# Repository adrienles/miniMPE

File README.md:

# miniMPE

An ultra-compact expressive octave-sectioned MIDI keyboard
## Idea

Originally inspired by the KORG nanoKeys line of ultra-compact MIDI keyboards, I wanted to design an alternative, with a few improvements:

- Standard key width
- Velocity sensitivity
    - The nanoKeys is not velocity sensitive, as it uses rubber-dome-like keys.
- RGB lighting for scale highlighting and pretty effects
- Daisy-chainable design, to go beyond a 2 octave design
    - This will likely be done using magnetic pogo pin connectors, for an easy and durable connection.
- Open Source :)
## Sub-projects
### MCU Test Board
This is a 4-layer test PCB designed to test one of the chosen MCU picks, alongside its dual USB peripherals, which this project might utilize.

#### Specs
- STM32F407 MCU
    - Dual USB peripherals
- IO header with dual SPI and 16 analog channels
- Dual USB ports
    - Output is protected against over-voltage
- Impedance matched USB and digital signals
- 4-layer design (Signal - Power/Gnd - Gnd - Signal)

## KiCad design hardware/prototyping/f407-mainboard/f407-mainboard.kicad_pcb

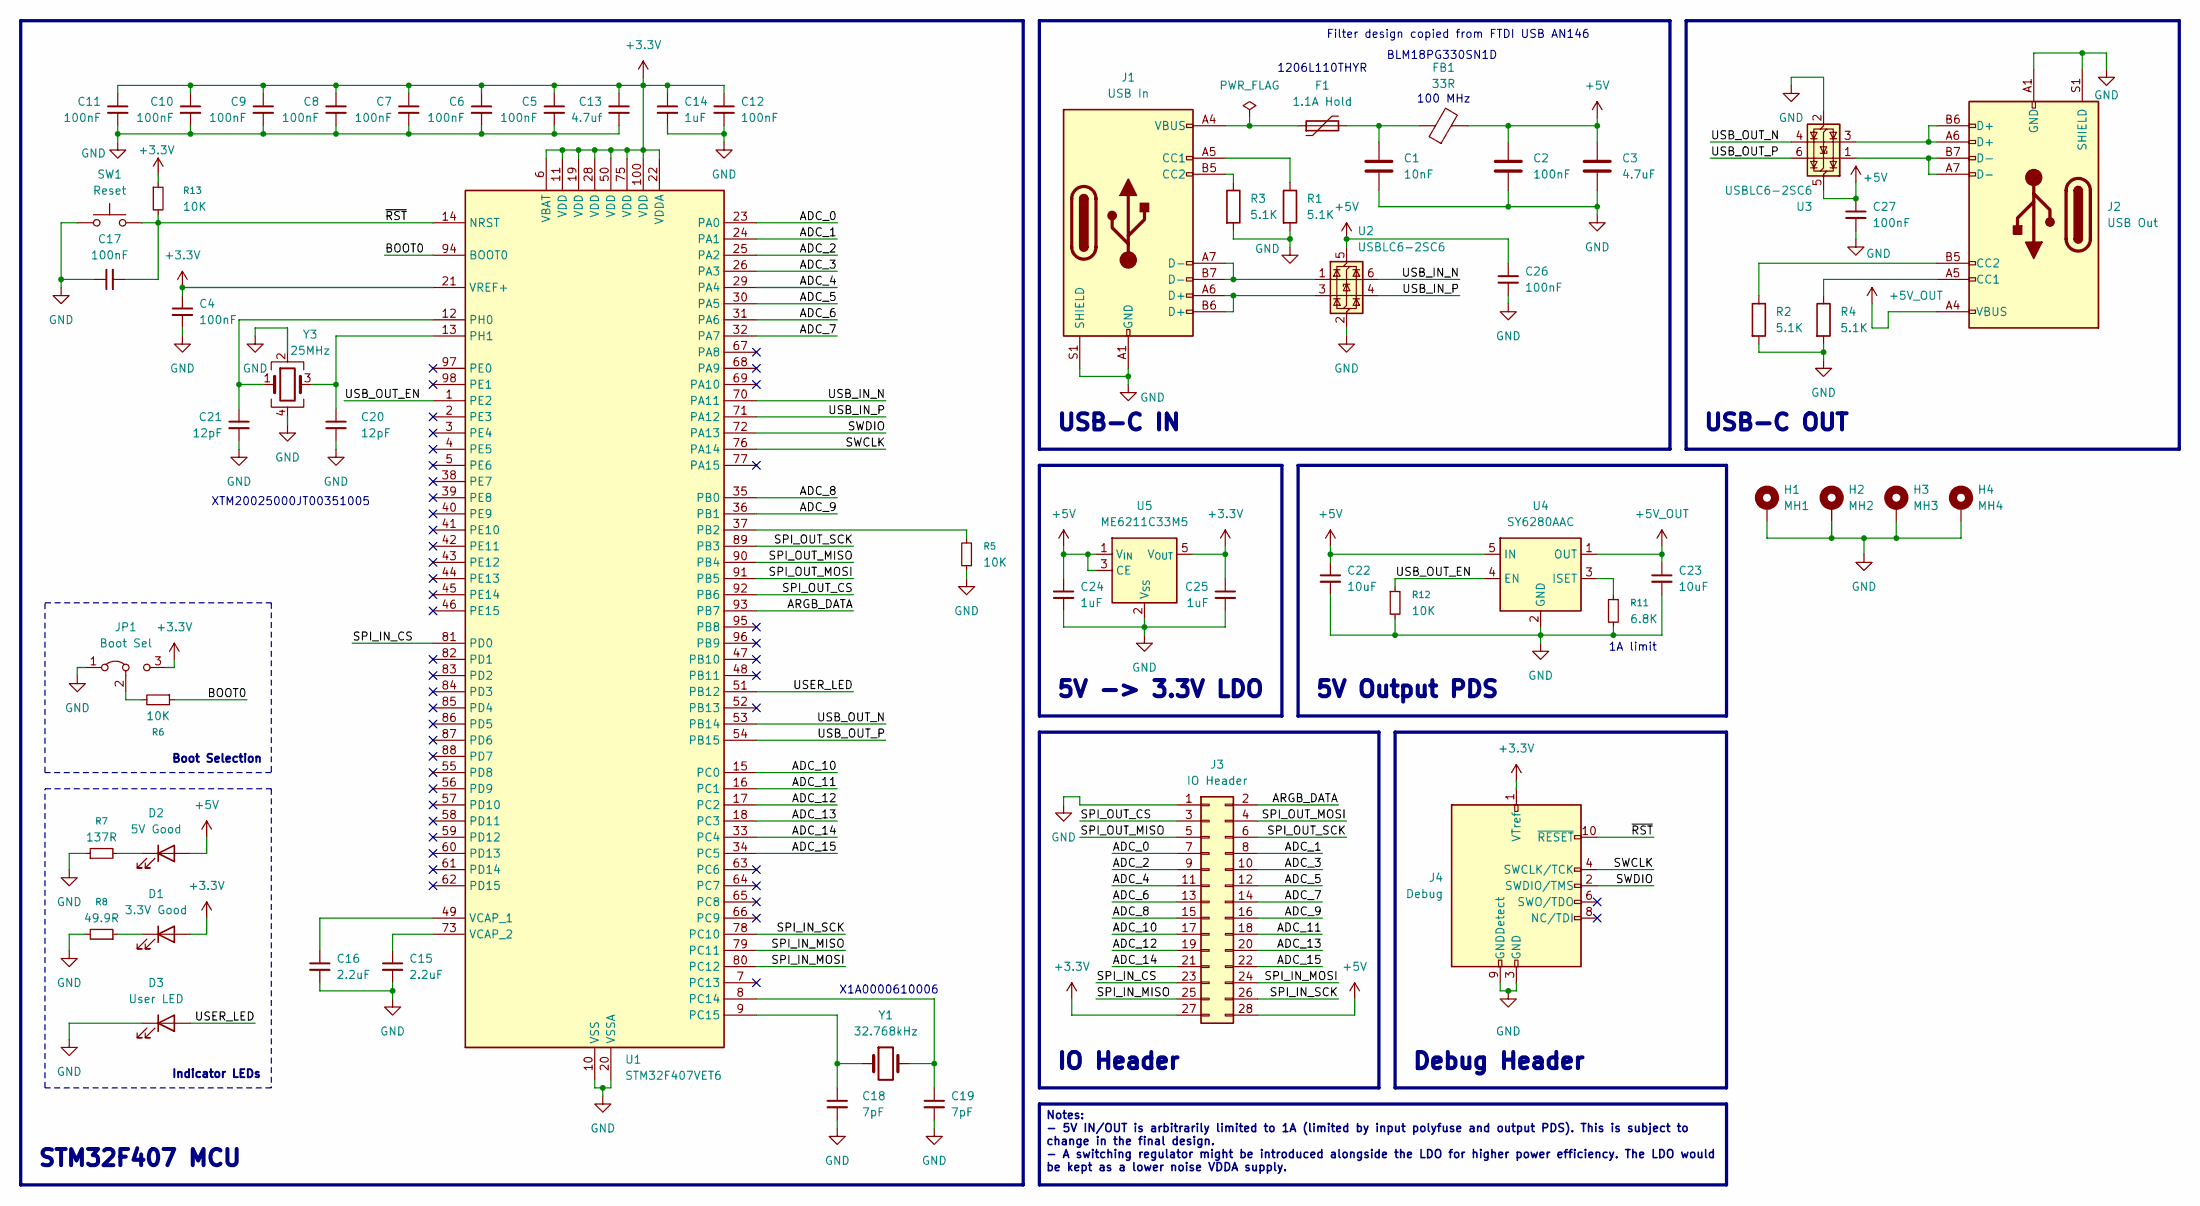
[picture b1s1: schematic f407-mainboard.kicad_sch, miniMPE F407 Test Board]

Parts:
C1: 10nF; C_0402_1005Metric
C2, C4, C5, C6, C7, C8, C9, C10, C11, C12, C17: 100nF; C_0402_1005Metric; LCSC C1525
C3: 4.7uF; C_0603_1608Metric
C13: 4.7uf; C_0402_1005Metric
C14: 1uF; C_0603_1608Metric
C15, C16: 2.2uF; C_0603_1608Metric
C18, C19: 7pF; C_0402_1005Metric
C20, C21: 12pF; C_0402_1005Metric
C22, C23: 10uF; C_0402_1005Metric
C24, C25: 1uF; C_0402_1005Metric
C26, C27: 100nF; C_0402_1005Metric
D1: 3.3V Good; LED_0603_1608Metric
D2: 5V Good; LED_0603_1608Metric
D3: User LED; LED_0603_1608Metric
F1: 1.1A Hold; Fuse_1206_3216Metric
FB1: 33R; L_0603_1608Metric
H1: MH1; MountingHole_3.2mm_M3_DIN965_Pad
H2: MH2; MountingHole_3.2mm_M3_DIN965_Pad
H3: MH3; MountingHole_3.2mm_M3_DIN965_Pad
H4: MH4; MountingHole_3.2mm_M3_DIN965_Pad
J1: USB In; USB_C_Receptacle_HRO_TYPE-C-31-M-12
J2: USB Out; USB_C_Receptacle_HRO_TYPE-C-31-M-12
J3: IO Header; PinSocket_2x14_P2.54mm_Horizontal
J4: Debug; PinHeader_2x05_P2.54mm_Vertical
JP1: Boot Sel; PinHeader_1x03_P2.54mm_Vertical
R1, R2, R3, R4: 5.1K; R_0402_1005Metric
R5, R6, R12, R13: 10K; R_0402_1005Metric
R7: 137R; R_0402_1005Metric
R8: 49.9R; R_0402_1005Metric
R11: 6.8K; R_0402_1005Metric
SW1: Reset; SW_SKRPACE010_AAL
U1: STM32F407VET6; LQFP-100_14x14mm_P0.5mm; LCSC C28730
U2, U3: USBLC6-2SC6; SOT-23-6; LCSC C7519
U4: SY6280AAC; SOT-23-5; LCSC C55136
U5: ME6211C33M5; SOT-23-5
Y1: 32.768kHz; Crystal_SMD_2012-2Pin_2.0x1.2mm
Y3: 25MHz; Crystal_SMD_2016-4Pin_2.0x1.6mm

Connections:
+3.3V: C4.1, C5.1, C6.1, C7.1, C8.1, C9.1, C10.1, C11.1, C12.1, C13.1, C14.1, C25.1, D1.2 (A), J3.27, J4.1 (VTref), JP1.3 (B), R13.1, U1.6 (VBAT), U1.11 (VDD), U1.19 (VDD), U1.21 (VREF+), U1.22 (VDDA), U1.28 (VDD), U1.50 (VDD), U1.75 (VDD), U1.100 (VDD), U5.5 (V_{OUT})
+5V: C2.1, C3.1, C22.1, C24.1, C26.1, C27.1, D2.2 (A), FB1.2, J3.28, U2.5 (VBUS), U3.5 (VBUS), U4.5 (IN), U5.1 (V_{IN}), U5.3 (CE)
+5V_OUT: C23.1, J2.A4 (VBUS), J2.A9 (VBUS), J2.B4 (VBUS), J2.B9 (VBUS), U4.1 (OUT)
/ADC_0: J3.7, U1.23 (PA0)
/ADC_1: J3.8, U1.24 (PA1)
/ADC_2: J3.9, U1.25 (PA2)
/ADC_3: J3.10, U1.26 (PA3)
/ADC_4: J3.11, U1.29 (PA4)
/ADC_5: J3.12, U1.30 (PA5)
/ADC_6: J3.13, U1.31 (PA6)
/ADC_7: J3.14, U1.32 (PA7)
/ADC_8: J3.15, U1.35 (PB0)
/ADC_9: J3.16, U1.36 (PB1)
/ADC_10: J3.17, U1.15 (PC0)
/ADC_11: J3.18, U1.16 (PC1)
/ADC_12: J3.19, U1.17 (PC2)
/ADC_13: J3.20, U1.18 (PC3)
/ADC_14: J3.21, U1.33 (PC4)
/ADC_15: J3.22, U1.34 (PC5)
/ARGB_DATA: J3.2, U1.93 (PB7)
/BOOT0: R6.1, U1.94 (BOOT0)
/SPI_IN_CS: J3.23, U1.81 (PD0)
/SPI_IN_MISO: J3.25, U1.79 (PC11)
/SPI_IN_MOSI: J3.24, U1.80 (PC12)
/SPI_IN_SCK: J3.26, U1.78 (PC10)
/SPI_OUT_CS: J3.3, U1.92 (PB6)
/SPI_OUT_MISO: J3.5, U1.90 (PB4)
/SPI_OUT_MOSI: J3.4, U1.91 (PB5)
/SPI_OUT_SCK: J3.6, U1.89 (PB3)
/SWCLK: J4.4 (SWCLK/TCK), U1.76 (PA14)
/SWDIO: J4.2 (SWDIO/TMS), U1.72 (PA13)
/USB_IN_N: U1.70 (PA11), U2.6 (I/O1)
/USB_IN_P: U1.71 (PA12), U2.4 (I/O2)
/USB_OUT_EN: R12.1, U1.1 (PE2), U4.4 (EN)
/USB_OUT_N: U1.53 (PB14), U3.4 (I/O2)
/USB_OUT_P: U1.54 (PB15), U3.6 (I/O1)
/USER_LED: D3.2 (A), U1.51 (PB12)
/~RST: C17.2, J4.10 (~RESET), R13.2, SW1.2, U1.14 (NRST)
GND: C1.2, C2.2, C3.2, C4.2, C5.2, C6.2, C7.2, C8.2, C9.2, C10.2, C11.2, C12.2, C13.2, C14.2, C15.2, C16.2, C17.1, C18.2, C19.2, C20.2, C21.2, C22.2, C23.2, C24.2, C25.2, C26.2, C27.2, D3.1 (K), H1.1, H2.1, H3.1, H4.1, J1.A1 (GND), J1.A12 (GND), J1.B1 (GND), J1.B12 (GND), J1.S1 (SHIELD), J2.A1 (GND), J2.A12 (GND), J2.B1 (GND), J2.B12 (GND), J2.S1 (SHIELD), J3.1, J4.3 (GND), J4.5 (GND), J4.9 (GNDDetect), JP1.1 (A), R1.2, R2.2, R3.2, R4.2, R5.1, R7.1, R8.2, R11.2, R12.2, SW1.1, U1.10 (VSS), U1.20 (VSSA), U1.27 (VSS), U1.74 (VSS), U1.99 (VSS), U2.2 (GND), U3.2 (GND), U4.2 (GND), U5.2 (V_{SS}), Y3.2, Y3.4
unnamed: C1.1, F1.2, FB1.1
unnamed: D1.1 (K), R8.1
unnamed: D2.1 (K), R7.2
unnamed: F1.1, J1.A4 (VBUS), J1.A9 (VBUS), J1.B4 (VBUS), J1.B9 (VBUS)
unnamed: J1.A5 (CC1), R1.1
unnamed: J1.B5 (CC2), R3.1
unnamed: J1.A6 (D+), J1.B6 (D+), U2.3 (I/O2)
unnamed: J1.A7 (D-), J1.B7 (D-), U2.1 (I/O1)
unnamed: J2.A5 (CC1), R4.1
unnamed: J2.B5 (CC2), R2.1
unnamed: J2.A6 (D+), J2.B6 (D+), U3.3 (I/O2)
unnamed: J2.A7 (D-), J2.B7 (D-), U3.1 (I/O1)
unnamed: JP1.2 (C), R6.2
unnamed: R5.2, U1.37 (PB2)
unnamed: C19.1, U1.8 (PC14), Y1.2
unnamed: C18.1, U1.9 (PC15), Y1.1
unnamed: C21.1, U1.12 (PH0), Y3.1
unnamed: C20.1, U1.13 (PH1), Y3.3
unnamed: C16.1, U1.49 (VCAP_1)
unnamed: C15.1, U1.73 (VCAP_2)
unnamed: R11.1, U4.3 (ISET)

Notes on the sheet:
USB-C IN
Indicator LEDs
Boot Selection
1206L110THYR
BLM18PG330SN1D
Debug Header
XTM20025000JT00351005
USB-C OUT
STM32F407 MCU
X1A0000610006
Filter design copied from FTDI USB AN146
100 MHz
5V -> 3.3V LDO
IO Header
1A limit
5V Output PDS
Notes: - 5V IN/OUT is arbitrarily limited to 1A (limited by input polyfuse and output PDS). This is subject to change in the final design. - A switching regulator might be introduced alongside the LDO for higher power efficiency. The LDO would be kept as a lower noise VDDA supply.

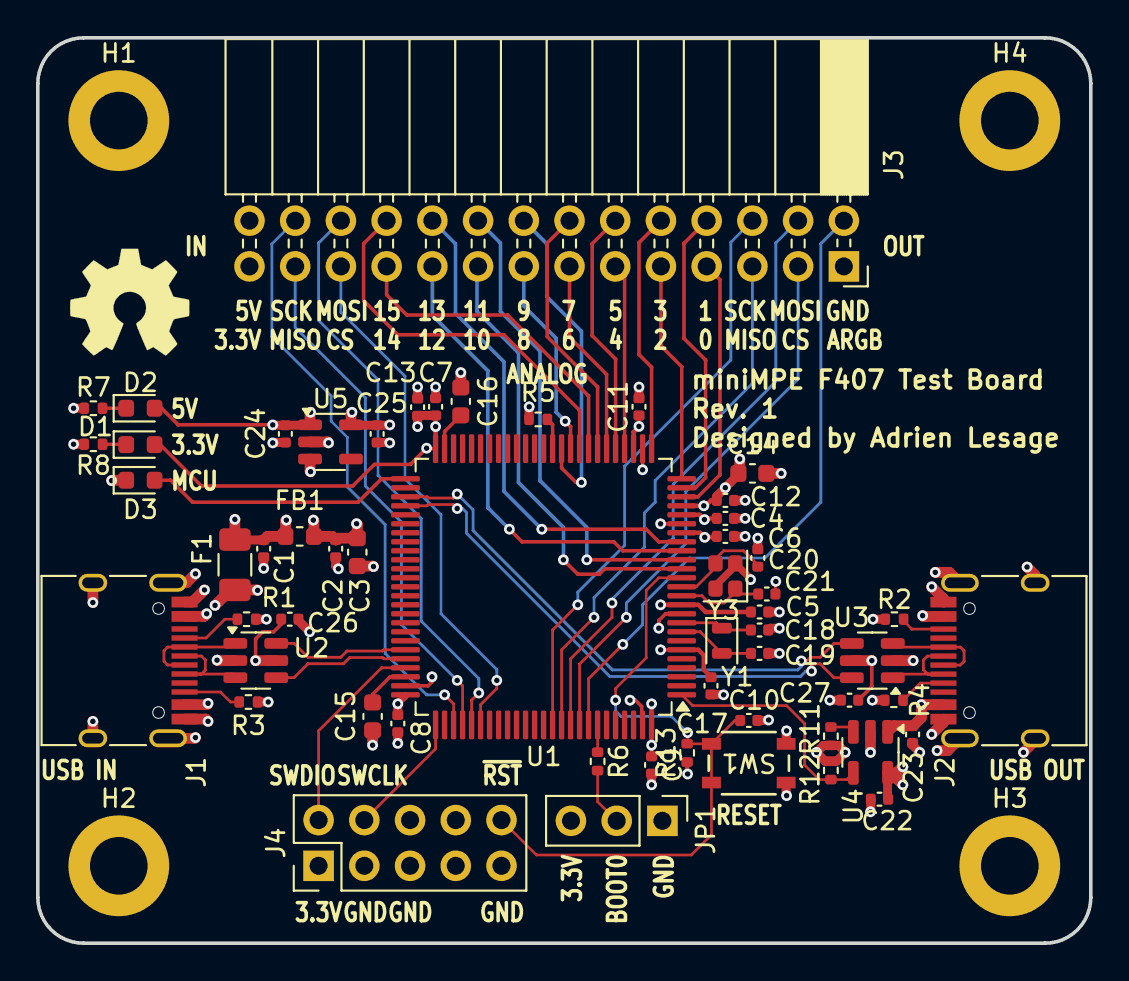
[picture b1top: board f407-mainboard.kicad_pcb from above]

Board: 4 copper layers, 58.5 x 50.3 mm, 60 parts (0 on the bottom side), 60 nets.

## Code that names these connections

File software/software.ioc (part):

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Mcu.Name=STM32F407V(E-G)Tx
Mcu.Package=LQFP100
Mcu.UserName=STM32F407VETx
PA0-WKUP.Signal=ADCx_IN0
PA1.Signal=ADCx_IN1
PA11.Mode=Device_Only
PA11.Signal=USB_OTG_FS_DM
PA12.Mode=Device_Only
PA12.Signal=USB_OTG_FS_DP
PA13.Mode=Serial_Wire
PA13.Signal=SYS_JTMS-SWDIO
PA14.Mode=Serial_Wire
PA14.Signal=SYS_JTCK-SWCLK
PA2.Signal=ADCx_IN2
PA3.Signal=ADCx_IN3
PA4.Signal=ADCx_IN4
PA5.Signal=ADCx_IN5
PA6.Signal=ADCx_IN6
PA7.Signal=ADCx_IN7
PB0.Signal=ADCx_IN8
PB1.Signal=ADCx_IN9
PB14.Mode=Host_FS
PB14.Signal=USB_OTG_HS_DM
PB15.Mode=Host_FS
PB15.Signal=USB_OTG_HS_DP
PB3.Mode=Full_Duplex_Master
PB3.Signal=SPI1_SCK
PB4.Mode=Full_Duplex_Master
PB4.Signal=SPI1_MISO
PB5.Mode=Full_Duplex_Master
PB5.Signal=SPI1_MOSI
PB6.Mode=I2C
PB6.Signal=I2C1_SCL
PB7.Mode=I2C
PB7.Signal=I2C1_SDA
PC0.Signal=ADCx_IN10
PC1.Signal=ADCx_IN11
PC10.Mode=Asynchronous
PC10.Signal=UART4_TX
PC11.Mode=Asynchronous
PC11.Signal=UART4_RX
PC14-OSC32_IN.Mode=LSE-External-Oscillator
PC14-OSC32_IN.Signal=RCC_OSC32_IN
PC15-OSC32_OUT.Mode=LSE-External-Oscillator
PC15-OSC32_OUT.Signal=RCC_OSC32_OUT
PC2.Signal=ADCx_IN12
PC3.Signal=ADCx_IN13
PC4.Signal=ADCx_IN14
PC5.Signal=ADCx_IN15
PD10.Signal=GPIO_Output
PH0-OSC_IN.Mode=HSE-External-Oscillator
PH0-OSC_IN.Signal=RCC_OSC_IN
PH1-OSC_OUT.Mode=HSE-External-Oscillator
PH1-OSC_OUT.Signal=RCC_OSC_OUT
RCC.HSE_VALUE=25000000
RCC.SYSCLKFreq_VALUE=16000000
board=custom

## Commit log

2026-01-16 ADD : Completed STM32F407 Test board. Readme
